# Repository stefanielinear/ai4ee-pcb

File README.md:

# ai4ee-pcb

[简体中文](README.zh-CN.md)

A collection of PCB projects that are automatically designed and generated by AI.

All projects are designed in **KiCad**. This repository hosts PCB projects produced by an AI agent (LLM toolchain) end to end — from requirements specification and part selection, through schematic entry, layout and routing, design review, to fabrication file export. Each sub-project lives in its own directory and can be opened directly in KiCad; it ships with the design sources, design documentation, and a fabrication package.

## Sub-projects

| Sub-project | Description | Status | Model / tokens |
| --- | --- | --- | --- |
| [ECG12_Portable](ECG12_Portable/README.md) | Portable 12-lead ECG acquisition board (engineering sample): KiCad 10, 45 × 45 mm 4-layer board, 110 purchased components, 14 test points, 6 double-sided fiducials, Rev B | Routed (native ERC / DRC: 0 violations, 0 unconnected), prototype validation pending | GPT-6 High, ~580k tokens |

## License

[Apache License 2.0](LICENSE)

> ⚠️ Each sub-project is an engineering sample and does **not** represent medical-device certification. For projects that interface with the human body (e.g., ECG), safety and compliance must be assessed separately per the documentation in the sub-project.

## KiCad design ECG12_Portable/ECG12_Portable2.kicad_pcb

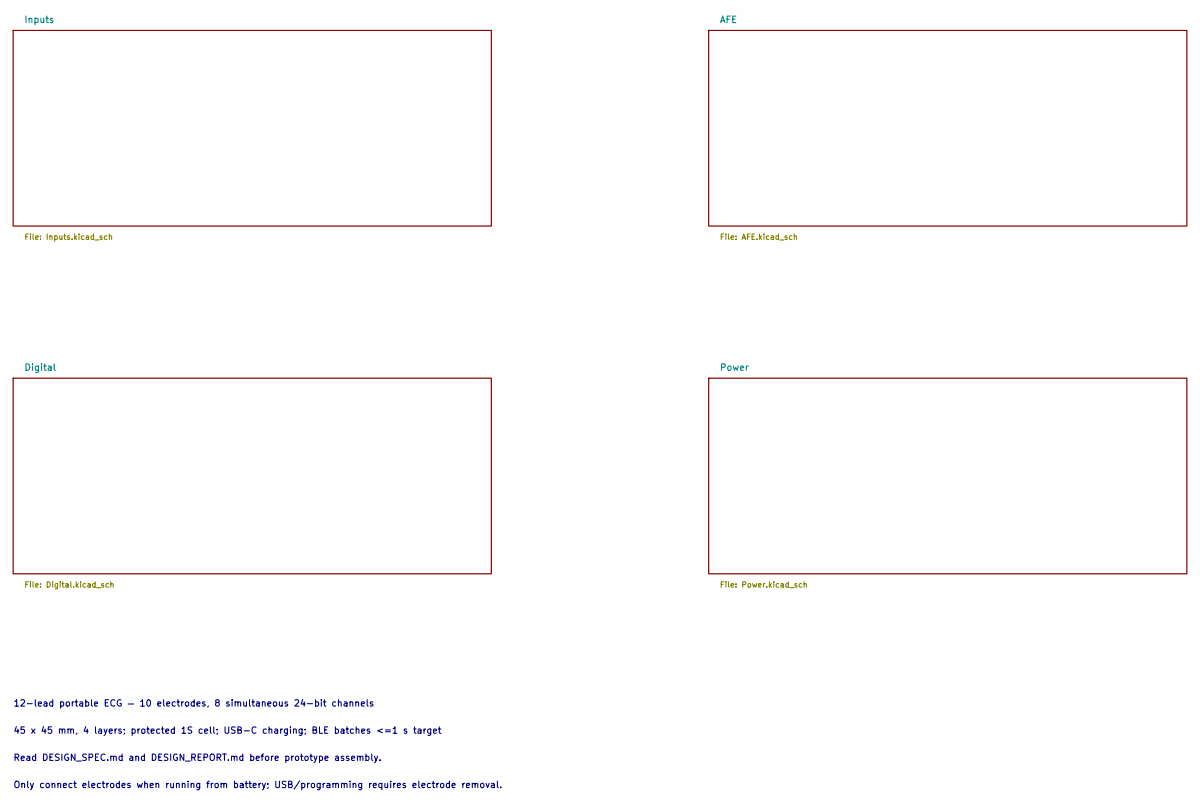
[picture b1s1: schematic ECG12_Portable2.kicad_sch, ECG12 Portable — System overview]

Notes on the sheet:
12-lead portable ECG — 10 electrodes, 8 simultaneous 24-bit channels
45 x 45 mm, 4 layers; protected 1S cell; USB-C charging; BLE batches <=1 s target
Read DESIGN_SPEC.md and DESIGN_REPORT.md before prototype assembly.
Only connect electrodes when running from battery; USB/programming requires electrode removal.

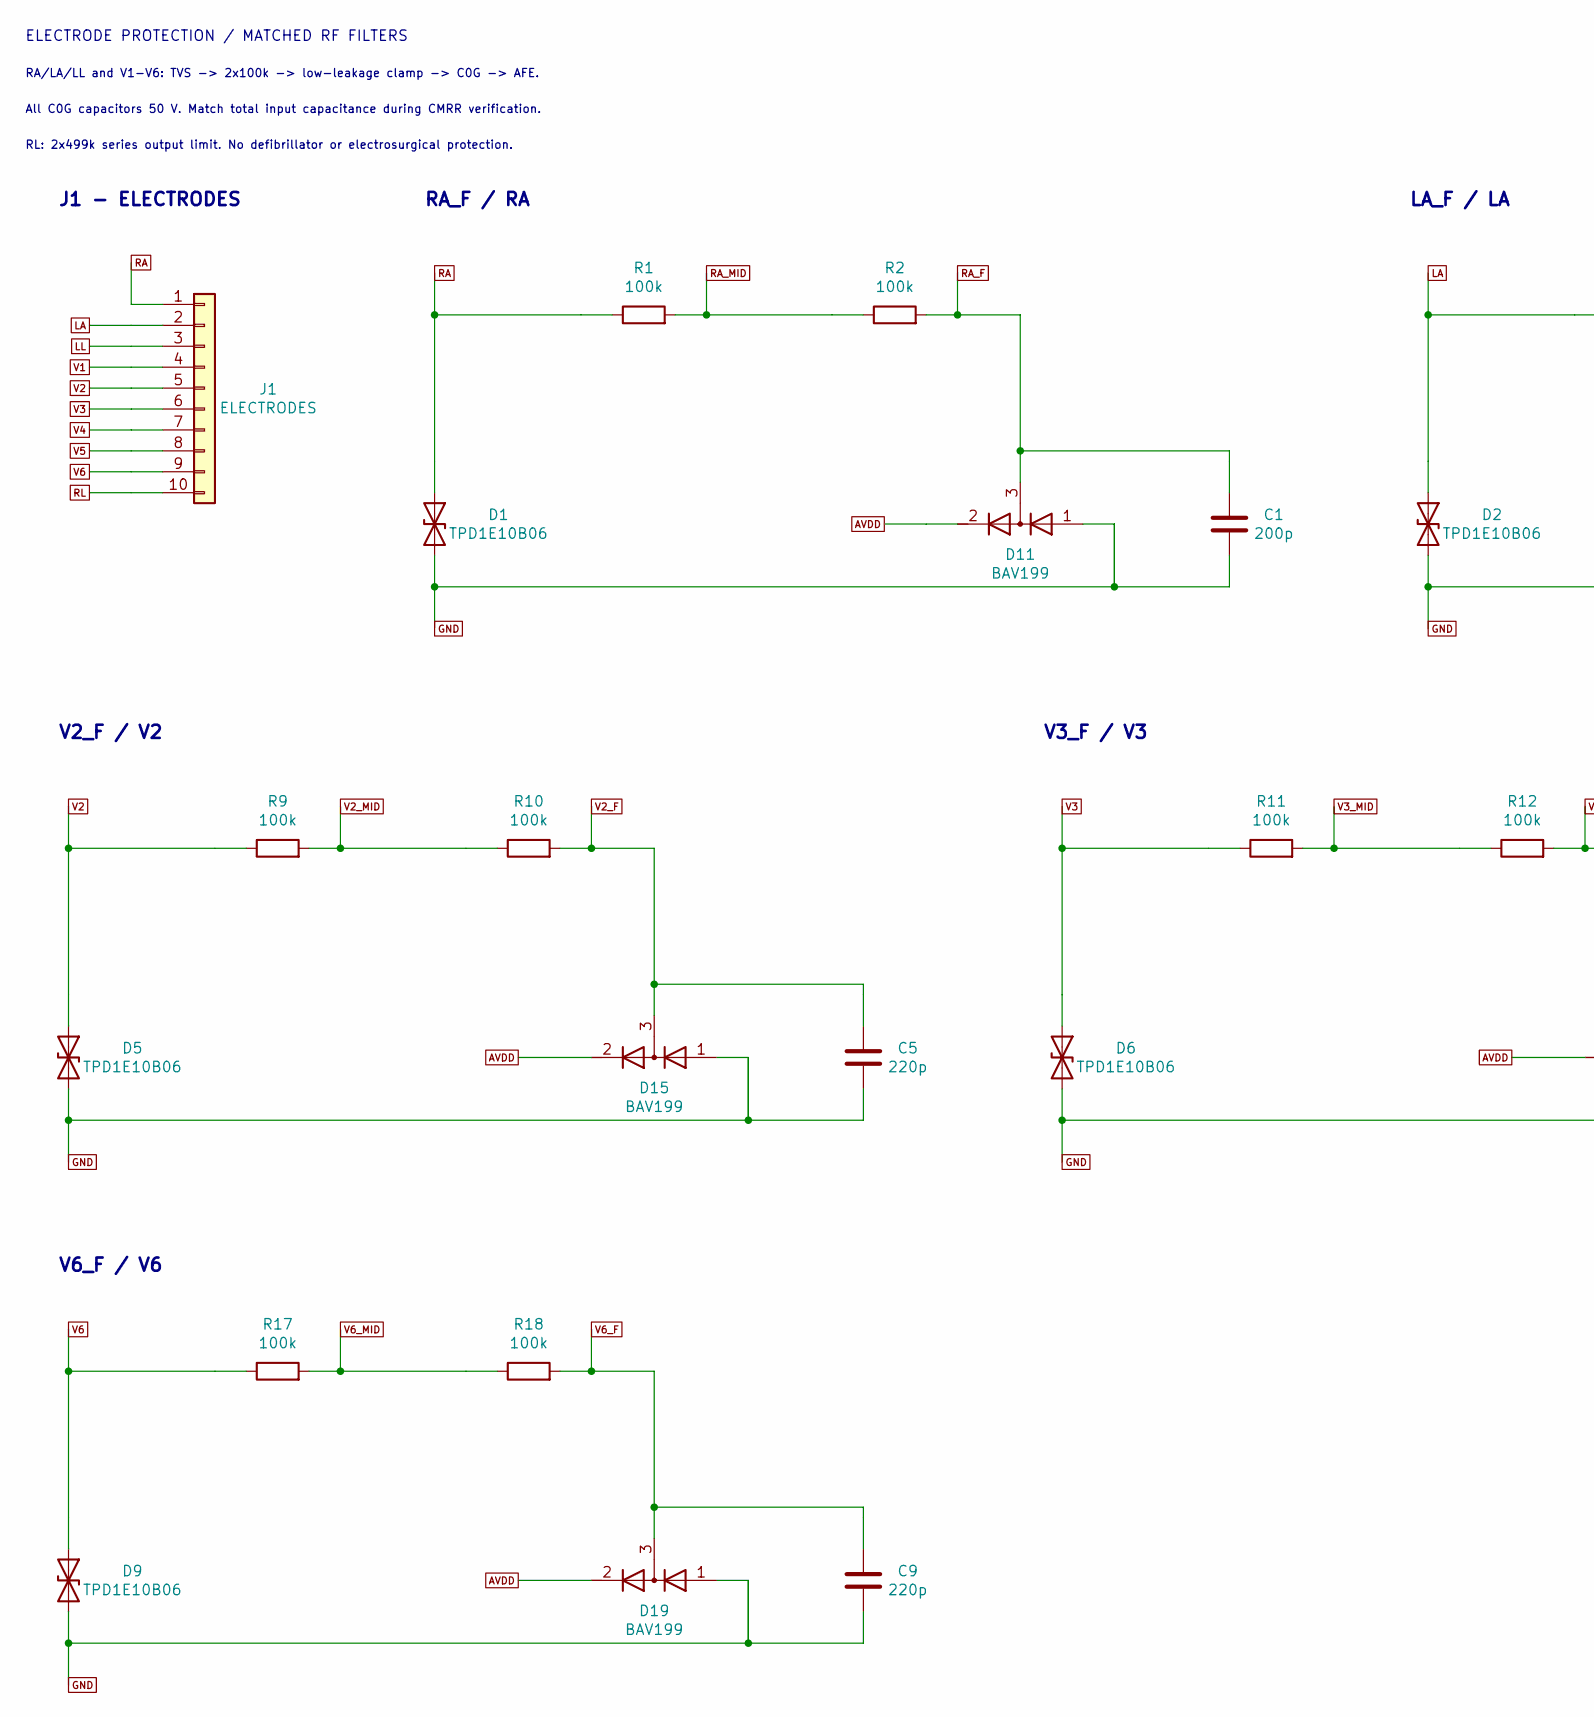
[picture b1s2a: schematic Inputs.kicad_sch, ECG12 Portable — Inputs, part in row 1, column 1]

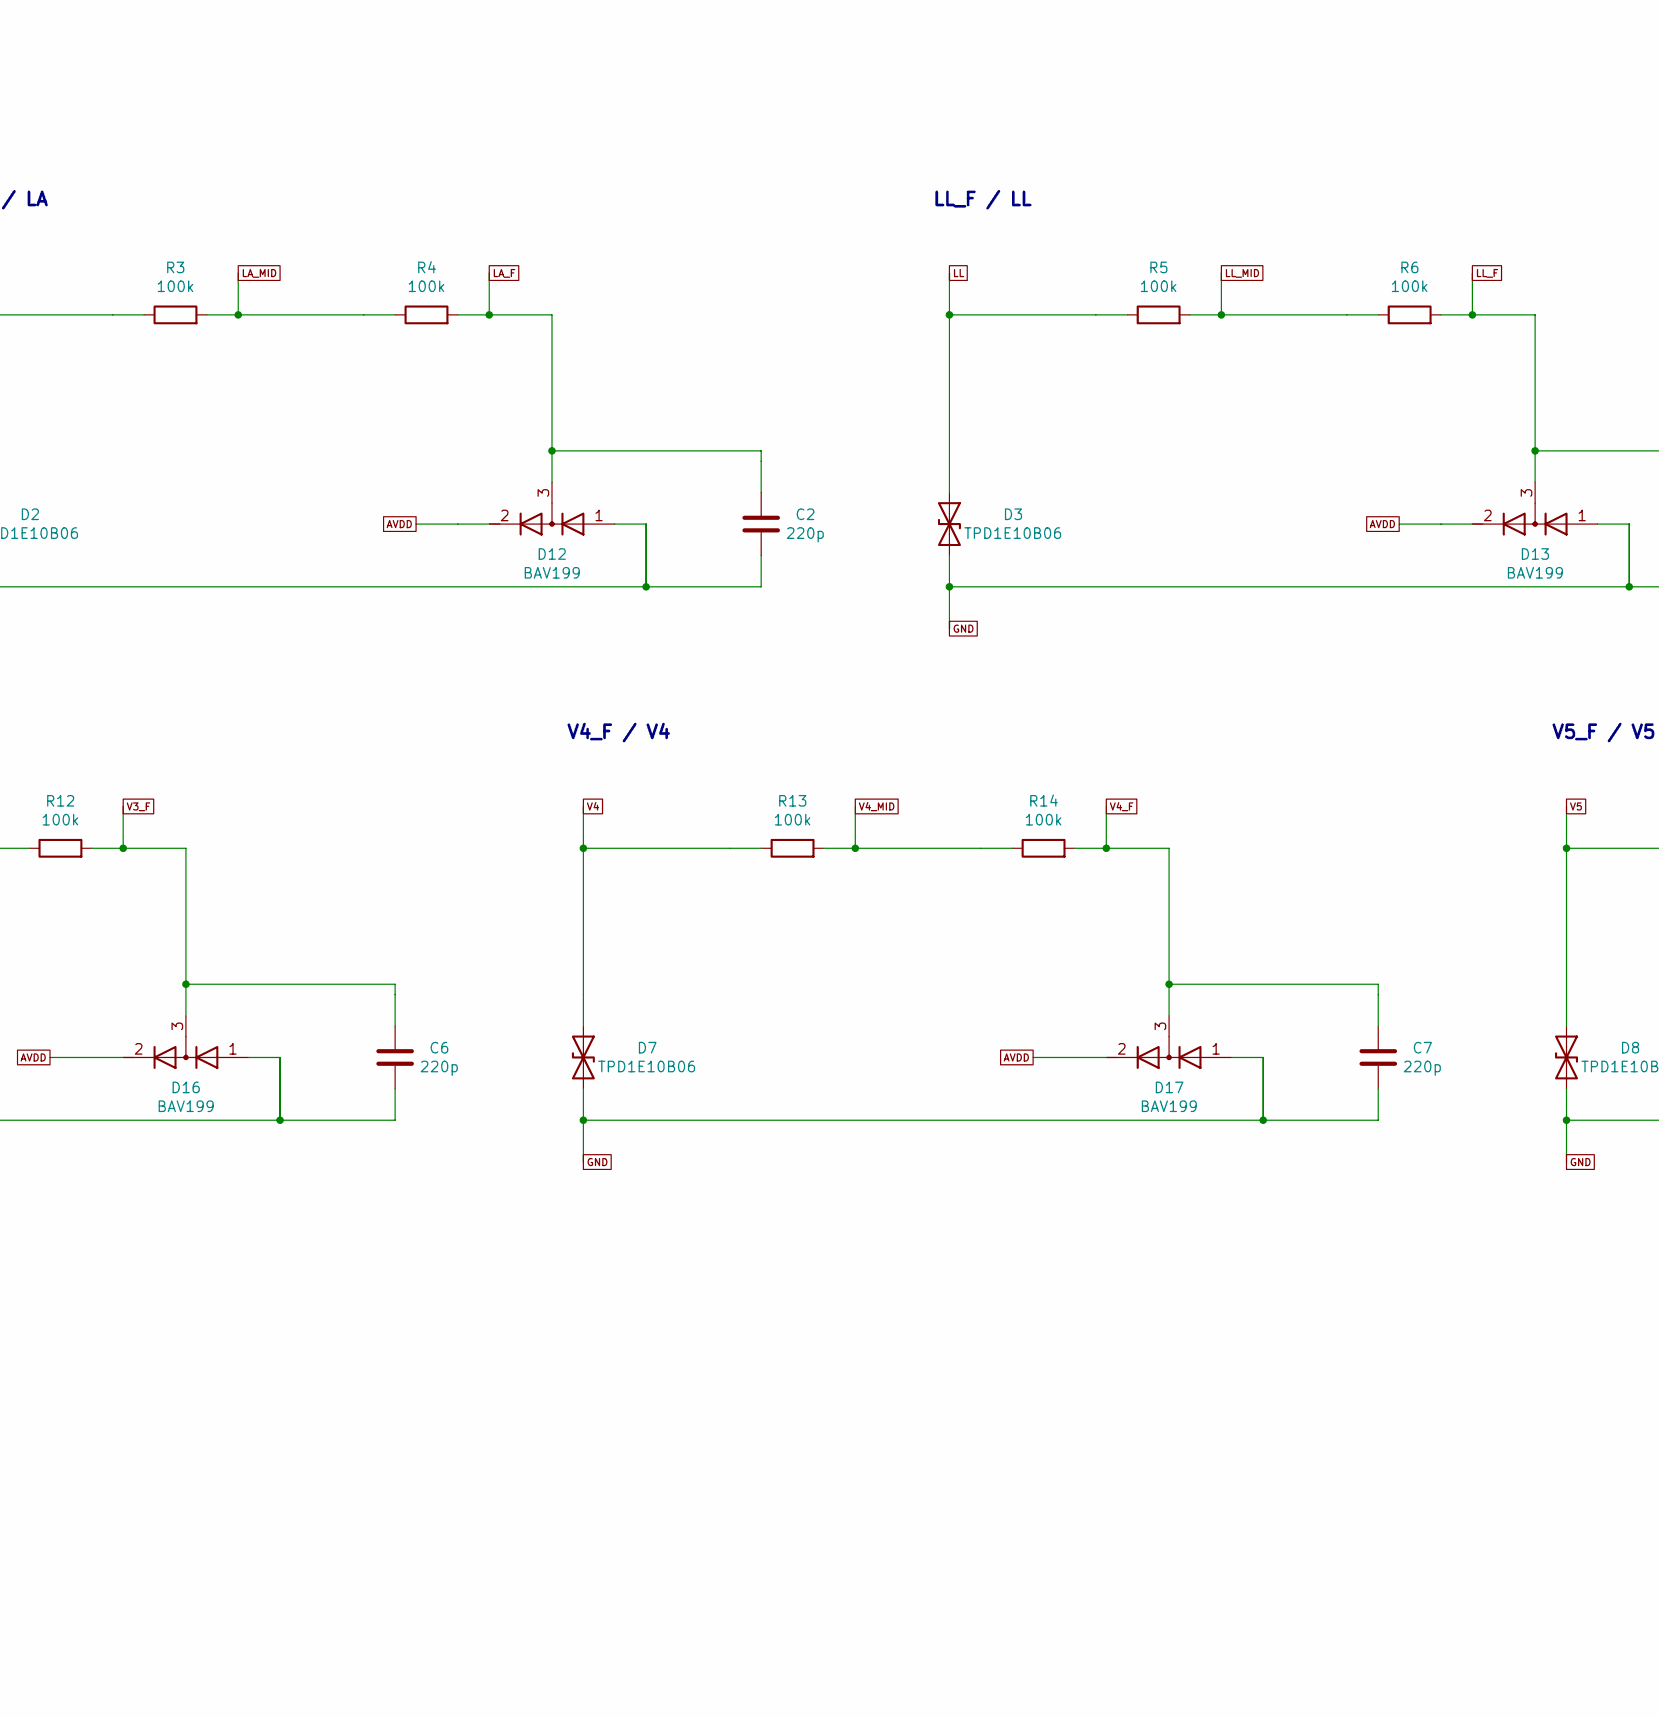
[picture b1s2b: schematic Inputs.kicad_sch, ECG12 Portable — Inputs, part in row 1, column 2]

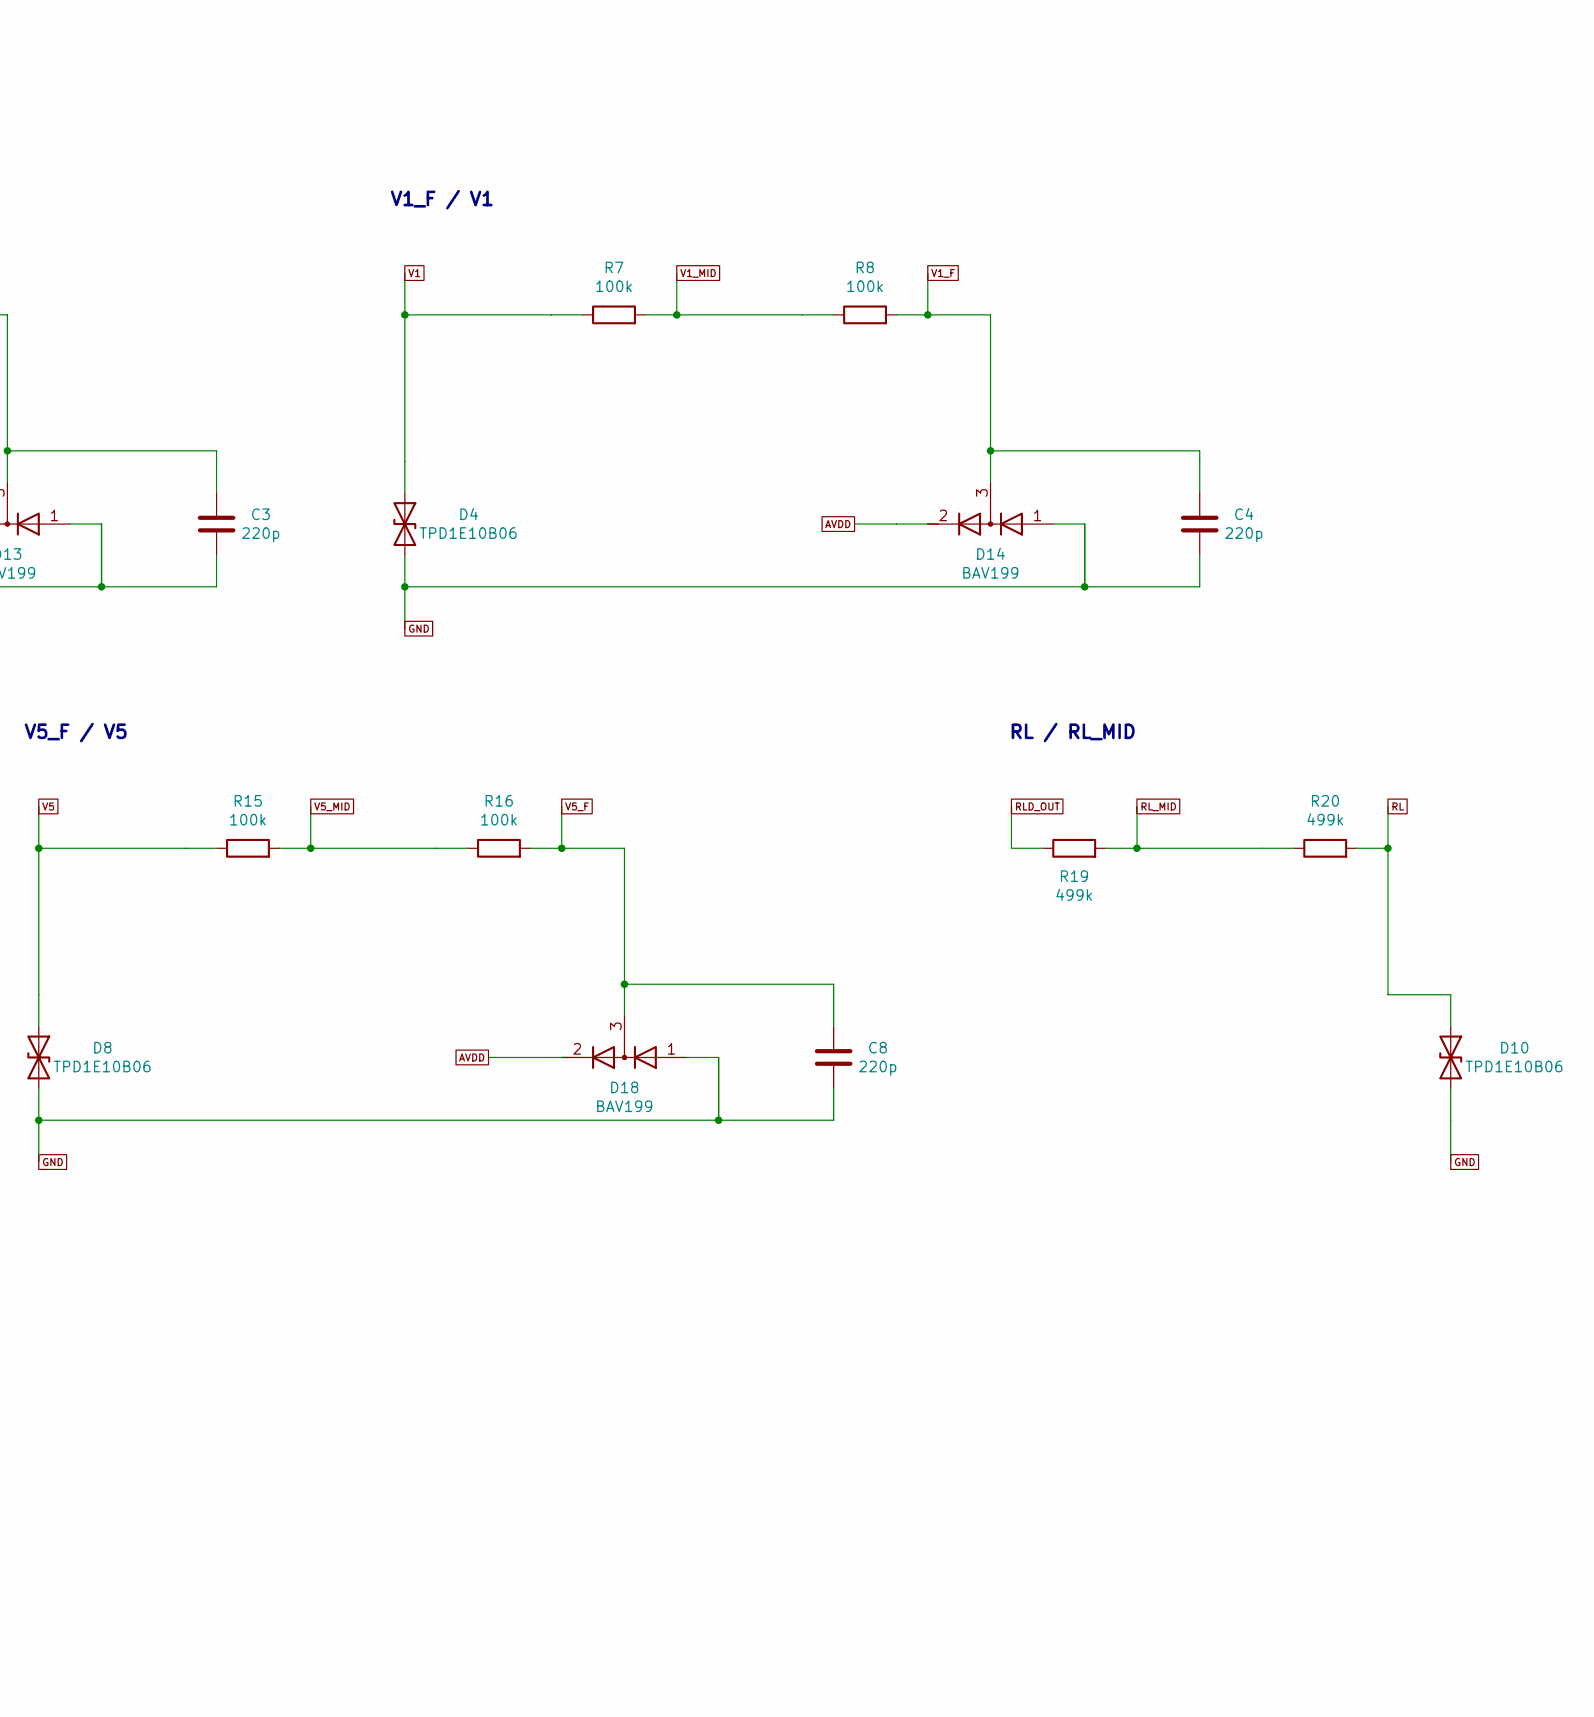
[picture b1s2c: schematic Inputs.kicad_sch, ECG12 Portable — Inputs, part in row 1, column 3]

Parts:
C1: 200p; Capacitor_SMD_C_0402_1005Metric; Tolerance 1%; Voltage 50V; MPN C0402C201F5GACTU
C2, C3, C4, C5, C6, C7, C8, C9: 220p; Capacitor_SMD_C_0402_1005Metric; Tolerance 1%; Voltage 50V; MPN C0402C221F5GACTU
D1, D2, D3, D4, D5, D6, D7, D8, D9, D10: TPD1E10B06; Diode_SMD_D_SOD-523; MPN TPD1E10B06DYAR
D11, D12, D13, D14, D15, D16, D17, D18, D19: BAV199; Package_TO_SOT_SMD_SOT-23; MPN BAV199,215
J1: ELECTRODES; Connector_JST_JST_SH_BM10B-SRSS-TB_1x10-1MP_P1.00mm_Vertical; MPN BM10B-SRSS-TB(LF)(SN)
R1, R2, R3, R4, R5, R6, R7, R8, R9, R10, R11, R12, R13, R14, R15, R16, R17, R18: 100k; Resistor_SMD_R_0402_1005Metric; MPN RT0402BRD07100KL
R19, R20: 499k; Resistor_SMD_R_0603_1608Metric; MPN RC0603FR-07499KL

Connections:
AVDD: D11.2 (K), D12.2 (K), D13.2 (K), D14.2 (K), D15.2 (K), D16.2 (K), D17.2 (K), D18.2 (K), D19.2 (K); also elsewhere on the board
GND: C1.2, C2.2, C3.2, C4.2, C5.2, C6.2, C7.2, C8.2, C9.2, D1.2 (A2), D2.2 (A2), D3.2 (A2), D4.2 (A2), D5.2 (A2), D6.2 (A2), D7.2 (A2), D8.2 (A2), D9.2 (A2), D10.2 (A2), D11.1 (A), D12.1 (A), D13.1 (A), D14.1 (A), D15.1 (A), D16.1 (A), D17.1 (A), D18.1 (A), D19.1 (A); also elsewhere on the board
LA: D2.1 (A1), J1.2, R3.1
LA_F: C2.1, D12.3 (common), R4.2; also elsewhere on the board
LA_MID: R3.2, R4.1
LL: D3.1 (A1), J1.3, R5.1
LL_F: C3.1, D13.3 (common), R6.2; also elsewhere on the board
LL_MID: R5.2, R6.1
RA: D1.1 (A1), J1.1, R1.1
RA_F: C1.1, D11.3 (common), R2.2; also elsewhere on the board
RA_MID: R1.2, R2.1
RL: D10.1 (A1), J1.10, R20.2
RLD_OUT: R19.1; also elsewhere on the board
RL_MID: R19.2, R20.1
V1: D4.1 (A1), J1.4, R7.1
V1_F: C4.1, D14.3 (common), R8.2; also elsewhere on the board
V1_MID: R7.2, R8.1
V2: D5.1 (A1), J1.5, R9.1
V2_F: C5.1, D15.3 (common), R10.2; also elsewhere on the board
V2_MID: R9.2, R10.1
V3: D6.1 (A1), J1.6, R11.1
V3_F: C6.1, D16.3 (common), R12.2; also elsewhere on the board
V3_MID: R11.2, R12.1
V4: D7.1 (A1), J1.7, R13.1
V4_F: C7.1, D17.3 (common), R14.2; also elsewhere on the board
V4_MID: R13.2, R14.1
V5: D8.1 (A1), J1.8, R15.1
V5_F: C8.1, D18.3 (common), R16.2; also elsewhere on the board
V5_MID: R15.2, R16.1
V6: D9.1 (A1), J1.9, R17.1
V6_F: C9.1, D19.3 (common), R18.2; also elsewhere on the board
V6_MID: R17.2, R18.1

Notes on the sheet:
ELECTRODE PROTECTION / MATCHED RF FILTERS
RA/LA/LL and V1-V6: TVS -> 2x100k -> low-leakage clamp -> C0G -> AFE.
All C0G capacitors 50 V. Match total input capacitance during CMRR verification.
RL: 2x499k series output limit. No defibrillator or electrosurgical protection.
J1 - ELECTRODES
RA_F / RA
LA_F / LA
LL_F / LL
V1_F / V1
V2_F / V2
V3_F / V3
V4_F / V4
V5_F / V5
V6_F / V6
RL / RL_MID

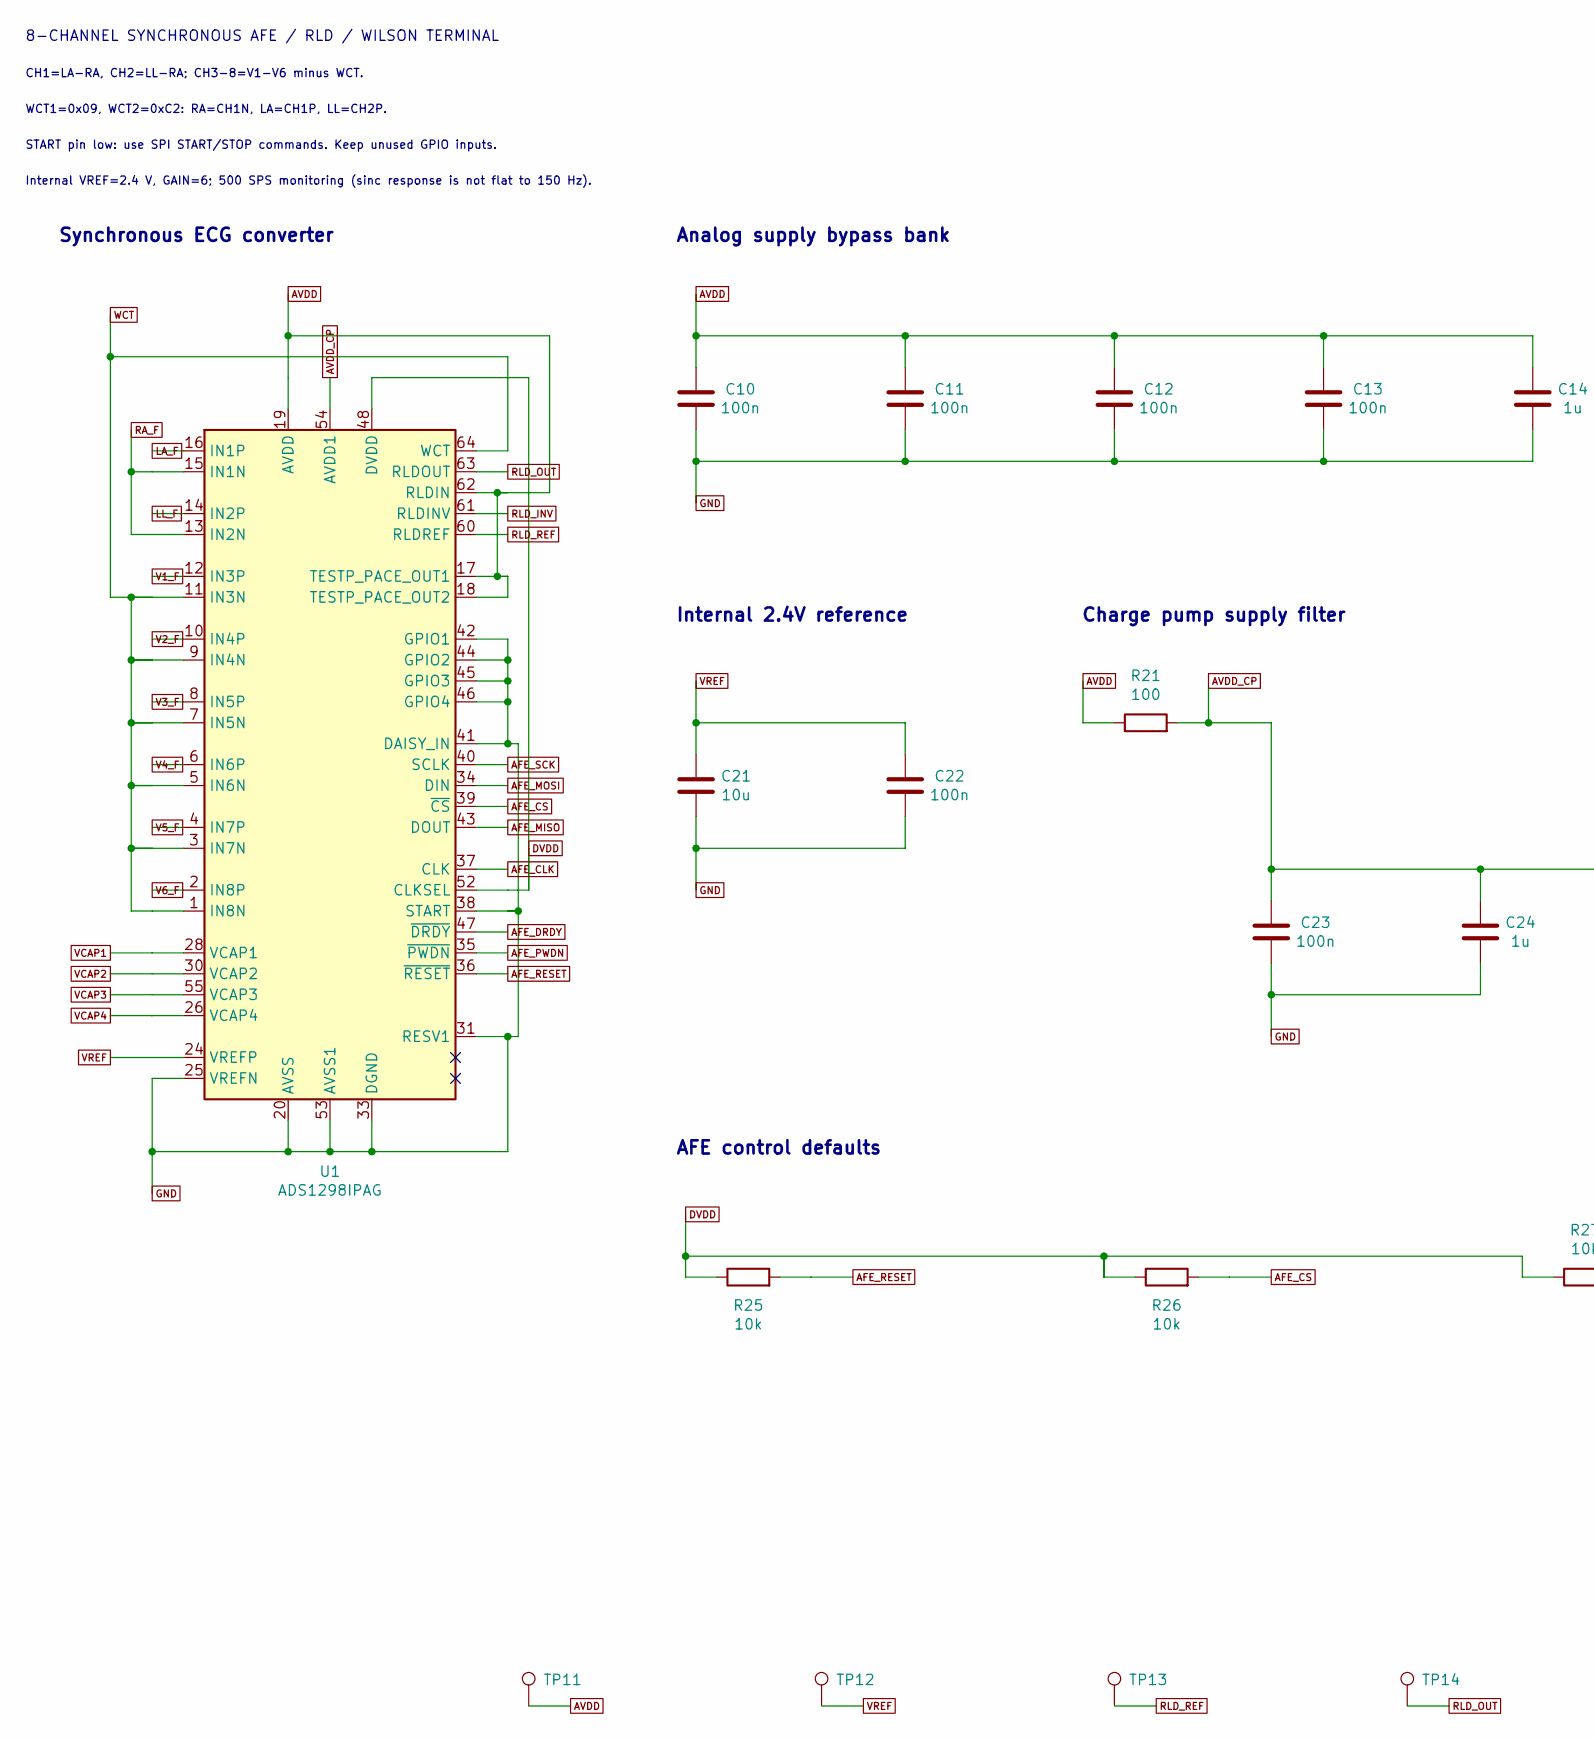
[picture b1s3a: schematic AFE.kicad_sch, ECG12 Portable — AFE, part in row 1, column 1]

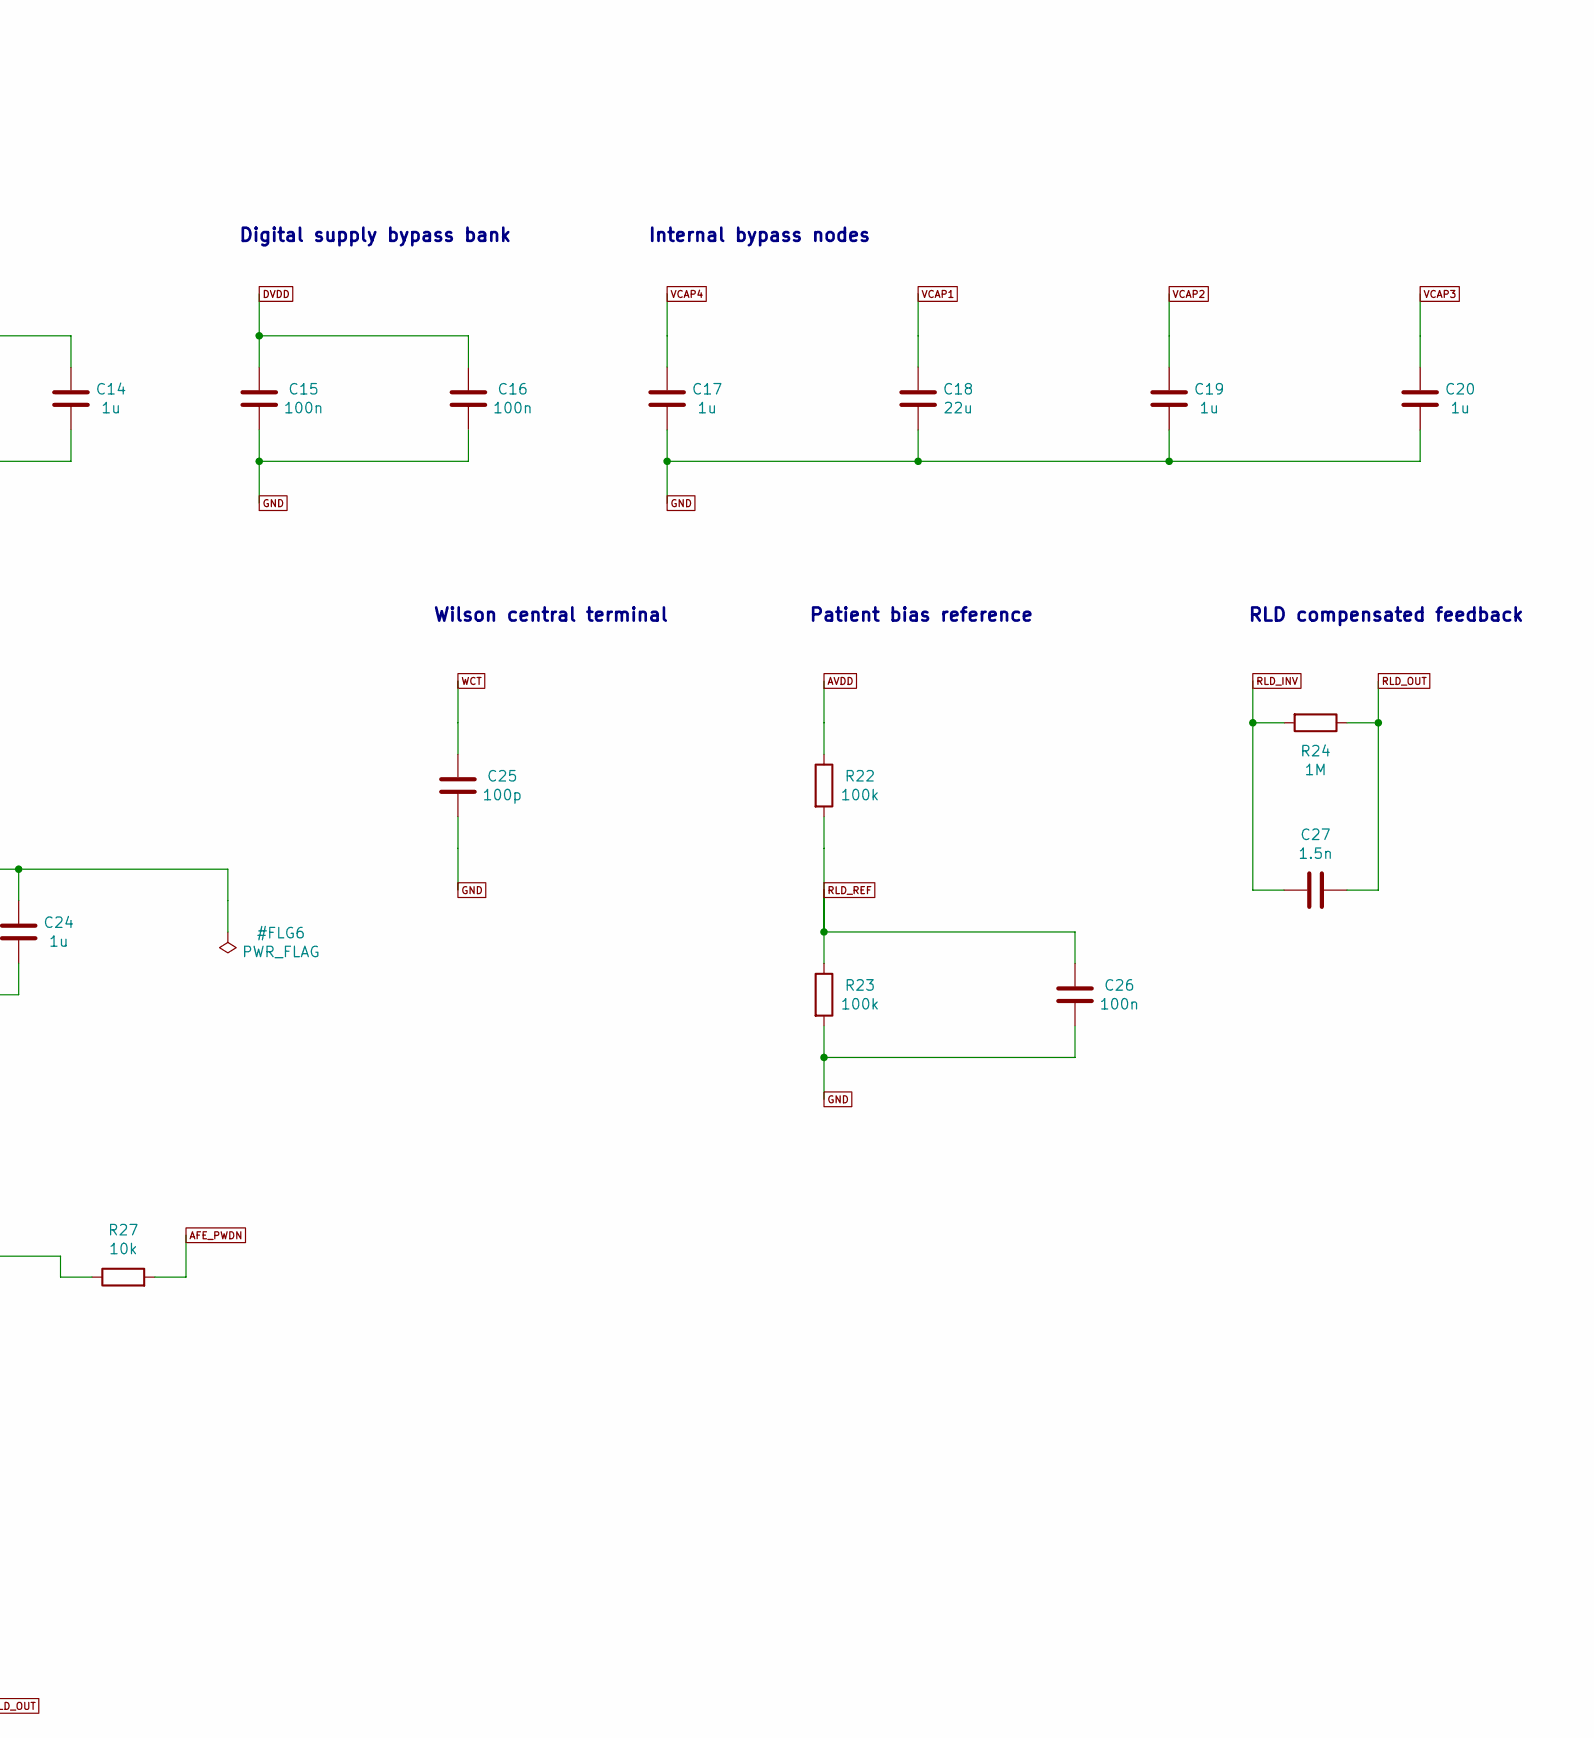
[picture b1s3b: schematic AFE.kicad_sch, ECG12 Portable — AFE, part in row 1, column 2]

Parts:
C10, C11, C12, C13, C15, C16, C22, C23, C26: 100n; Capacitor_SMD_C_0402_1005Metric; MPN GRM155R71C104KA88D
C14, C17, C19, C20, C24: 1u; Capacitor_SMD_C_0402_1005Metric; MPN GRM155R61A105KE15D
C18: 22u; Capacitor_SMD_C_0805_2012Metric; MPN GRM21BR60J226ME39L
C21: 10u; Capacitor_SMD_C_0603_1608Metric; MPN GRM188R60J106ME47D
C25: 100p; Capacitor_SMD_C_0402_1005Metric; MPN GRM1555C1H101JA01D
C27: 1.5n; Capacitor_SMD_C_0603_1608Metric; MPN GRM1885C1H152JA01D
R21: 100; Resistor_SMD_R_0402_1005Metric; MPN RC0402FR-07100RL
R22, R23: 100k; Resistor_SMD_R_0402_1005Metric; MPN RC0402FR-07100KL
R24: 1M; Resistor_SMD_R_0402_1005Metric; MPN RC0402FR-071ML
R25, R26, R27: 10k; Resistor_SMD_R_0402_1005Metric; MPN RC0402FR-0710KL
TP11: AVDD; TestPoint_TestPoint_Pad_D1.0mm; MPN TEST_PAD_1MM
TP12: VREF; TestPoint_TestPoint_Pad_D1.0mm; MPN TEST_PAD_1MM
TP13: RLD_REF; TestPoint_TestPoint_Pad_D1.0mm; MPN TEST_PAD_1MM
TP14: RLD_OUT; TestPoint_TestPoint_Pad_D1.0mm; MPN TEST_PAD_1MM
U1: ADS1298IPAG; Package_QFP_TQFP-64_10x10mm_P0.5mm; MPN ADS1298IPAG

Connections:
AFE_CLK: U1.37 (CLK); also elsewhere on the board
AFE_CS: R26.2, U1.39 (~CS); also elsewhere on the board
AFE_DRDY: U1.47 (~DRDY); also elsewhere on the board
AFE_MISO: U1.43 (DOUT); also elsewhere on the board
AFE_MOSI: U1.34 (DIN); also elsewhere on the board
AFE_PWDN: R27.2, U1.35 (~PWDN); also elsewhere on the board
AFE_RESET: R25.2, U1.36 (~RESET); also elsewhere on the board
AFE_SCK: U1.40 (SCLK); also elsewhere on the board
AVDD: C10.1, C11.1, C12.1, C13.1, C14.1, R21.1, R22.1, TP11.1, U1.17 (TESTP_PACE_OUT1), U1.18 (TESTP_PACE_OUT2), U1.19 (AVDD), U1.21 (AVDD), U1.22 (AVDD), U1.56 (AVDD), U1.59 (AVDD), U1.62 (RLDIN); also elsewhere on the board
AVDD_CP: C23.1, C24.1, R21.2, U1.54 (AVDD1)
DVDD: C15.1, C16.1, R25.1, R26.1, R27.1, U1.48 (DVDD), U1.50 (DVDD), U1.52 (CLKSEL); also elsewhere on the board
GND: C10.2, C11.2, C12.2, C13.2, C14.2, C15.2, C16.2, C17.2, C18.2, C19.2, C20.2, C21.2, C22.2, C23.2, C24.2, C25.2, C26.2, R23.2, U1.20 (AVSS), U1.23 (AVSS), U1.25 (VREFN), U1.31 (RESV1), U1.32 (AVSS), U1.33 (DGND), U1.38 (START), U1.41 (DAISY_IN), U1.42 (GPIO1), U1.44 (GPIO2), U1.45 (GPIO3), U1.46 (GPIO4), U1.49 (DGND), U1.51 (DGND), U1.53 (AVSS1), U1.57 (AVSS), U1.58 (AVSS); also elsewhere on the board
LA_F: U1.16 (IN1P); also elsewhere on the board
LL_F: U1.14 (IN2P); also elsewhere on the board
RA_F: U1.13 (IN2N), U1.15 (IN1N); also elsewhere on the board
RLD_INV: C27.2, R24.2, U1.61 (RLDINV)
RLD_OUT: C27.1, R24.1, TP14.1, U1.63 (RLDOUT); also elsewhere on the board
RLD_REF: C26.1, R22.2, R23.1, TP13.1, U1.60 (RLDREF)
V1_F: U1.12 (IN3P); also elsewhere on the board
V2_F: U1.10 (IN4P); also elsewhere on the board
V3_F: U1.8 (IN5P); also elsewhere on the board
V4_F: U1.6 (IN6P); also elsewhere on the board
V5_F: U1.4 (IN7P); also elsewhere on the board
V6_F: U1.2 (IN8P); also elsewhere on the board
VCAP1: C18.1, U1.28 (VCAP1)
VCAP2: C19.1, U1.30 (VCAP2)
VCAP3: C20.1, U1.55 (VCAP3)
VCAP4: C17.1, U1.26 (VCAP4)
VREF: C21.1, C22.1, TP12.1, U1.24 (VREFP)
WCT: C25.1, U1.1 (IN8N), U1.3 (IN7N), U1.5 (IN6N), U1.7 (IN5N), U1.9 (IN4N), U1.11 (IN3N), U1.64 (WCT)

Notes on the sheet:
8-CHANNEL SYNCHRONOUS AFE / RLD / WILSON TERMINAL
CH1=LA-RA, CH2=LL-RA; CH3-8=V1-V6 minus WCT.
WCT1=0x09, WCT2=0xC2: RA=CH1N, LA=CH1P, LL=CH2P.
START pin low: use SPI START/STOP commands. Keep unused GPIO inputs.
Internal VREF=2.4 V, GAIN=6; 500 SPS monitoring (sinc response is not flat to 150 Hz).
Synchronous ECG converter
Analog supply bypass bank
Digital supply bypass bank
Internal bypass nodes
Internal 2.4V reference
Charge pump supply filter
Wilson central terminal
Patient bias reference
RLD compensated feedback
AFE control defaults
